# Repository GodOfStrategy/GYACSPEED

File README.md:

# GYACSPEED
Speedometer, accelerometer and a gyroscope for my bicycle, with the XIAO RP2040 as the MCU, with a 2.4" TFT (no touchscreen) display (connected with jumpers) for the information.
I saw the Hermes starter project and though, "Why only stop at a gyroscope?" and then answered my own question by adding a speedometer powered by the Ublox NEO-M9N GNSS module, and a gyroscope and an accelerometer powered by the LSM6DSLTR!! So that I can see my speed, acceleration, and how I take turn using the gyroscope and such, with the XIAO RP2040 serving as my MCU. I made this project because, well, I thought that Hermes was cool but then realized that only a gyroscope isn't that useful after all. I thought about an all-in-one bicycle dashboard, complete with a speedometer, odometer (calculated from the GPS module), accelerometer (to see the derivative of velocity ;) ). My bicycle isn't really a smart bicycle so it doesn't have all these features built-in like some other smart bicycles.
So, I drew the Schematics:

Then I routed the PCB

How my assembled PCB is supposed to look like:

Then I designed a case in Fusion 360 for my project, and found solutions so as to how will I mount it on my bicycle and then came up with this monstrosity:

The idea of the mount is to be modular and help me join the two parts by using a single mount. The mount is based on the idea of mounting the project on my bicycle handle bar. I took some measurements and made a cylinder with walls which would wrap around my bicycle bar. After that I added an extension to the cylinder with a flat base, where I added the screw holes. I then added a triangular kind of part to join the cylinder with my main project case.

Instructions on Assembling:
1. Solder the Header Pins.
2. seat the pcb into the top case.
3. Now there is an opening in the bottom of the top case to allow jumpers from the Li-Po to connect with the Main PCB as shown here: 
4. The hole on the side of the bottom [battery] case looks like so: 
5. Run two jumpers connecting the Battery to the PCB, the left pin on the main PCB is the +ve terminal, as mentioned on the silkscreen.
6. There are mounting holes on tft module that I will be purchasing, and I have also added holes on my case top so that I can secure the display. To do so, we place the Display on the bottom of the top case like so:  and then insert bolts(M3/ 15mm) form the top : and screw them with the nuts tightly.
7. Then we again use jumper wires to connect the display to the pcb 
after which we place the top case cover on the top case and put 30 mm M3 bolts through the screw holes and secure them with M3 nuts.
8. For the bottom case, we insert our battery in the main bottom case, run the jumpers to the main PCB through the openings, and then We put the case cover on, and screw it using M3 30mm bolts and M3 nuts.
9. Now, we have two modules, to mount them together on a bicycle handlebar, we simply put them on the bicycle bar and then screw the both together in this mount-ish-part 
using the screw holes, and M3 15mm bolts along with M3 nuts.
Thats it! You're done

Here is my BoM (which you can find in the root of my repository as well):

|Designator|Footprint|Quantity|Value|LCSC Part #|Price (US $)|Links|Distributor|Generic Name|
|---|---|---|---|---|---|---|---|---|
| C1 | 805 | 5.0 | 100uF |  | 3.54 | GRM21BR60E107ME15K Murata Electronics \| Mouser India | Mouser India | Capacitors |
| C10, C3, C4, C5 | 402 | 10.0 | 10uF |  | 0.46 | https://www.mouser.in/ProductDetail/TAIYO-YUDEN/MSASJ105CB5106MFNC12?qs=PBDs2xEllI8xKzMj03Wyvw%3D%3D | Mouser India |  |
| C11, C12, C7, C8, C9 | 402 | 5.0 | 0.1uF |  | 0.24 | https://www.mouser.in/ProductDetail/80-C0402C104K4P | Mouser India |  |
| C2 | 402 | 1.0 | 1pF |  | 0.25 | 04023A1R0DAT2A KYOCERA AVX \| Mouser India |  |  |
| C6 | 402 | 10.0 | 1uF |  | 0.17 | https://www.mouser.in/ProductDetail/KYOCERA-AVX/0402X5R105KTAAT?qs=XAiT9M5g4x9uZyL2wCxs9w%3D%3D | Mouser India |  |
| D1 | D_SMA | 3.0 | SS14 |  | 1.3 | https://www.mouser.in/ProductDetail/onsemi/SS14?qs=mVVXn4M53U%252BvrBaFv5vr4w%3D%3D | Mouser India | Reverse Polarity Protection diode |
| DS1 | TFT LCD 240x320 2.4" | 2.0 | TFT LCD 2.4" SPI |  | 16.53 | [https://www.amazon.in/Tishvi-Interface-Contrast-Microcontroller-Projects/dp/B0GZQBH8TX/ref=sr_1_5?](https://www.amazon.in/SmartElex-2-4-inch-Interface-Resolution-Embedded/dp/B0GFD2GKS3/ref=sr_1_4?crid=244DTUY4MZBQU&dib=eyJ2IjoiMSJ9.mDHIa2KAK2pmYUCsQJKHijIuZuYtAhf37UUXZ595NunUV92PkwKzGlaTkl74UG3vta_Y1FTv8jmFhQ4SpozWyYBP9G75R6iKsYMW7jx-yHz3v-XOoo8-NUCHxRbKeTt5cD8Obvwvtn8YszEZtxFSuAXtiARzswfbkZinJIO2O0KPUdrK37qG1dR4FZ4mwfbZ0ufkE-BBbzZWaG5fWrOaPU771ftGh-Zgijp7mwLvgODtW0shDh-DNo6jAhYBoJCUGXP24-NSn2eDBEwA2ogDf_CD-Ctqugaj9IkxcIXHBB4.f5dMLYGoDtHfcPthudfcRWmNg96l1DWC8e63EOn9BP8&dib_tag=se&keywords=3+inch+tft+lcd&qid=1785163110&sprefix=3+inch+tft+lc%2Caps%2C434&sr=8-4)crid=5ELFGR2Y3AVB&dib=eyJ2IjoiMSJ9.Jpr0nalYGfL14nV7bbjmTZKJv2EIKupA4PS6ncRHPeflKUuEP1chaxLUuG31tnS91O83QhHNpJtINdHxloWLYH9lf4NJ4qSOWR6nymU5ejpQAXrm3idjtpBYQ0aIwBILTmNX_3lALKvsE76wo-qvywPqliJmu2u1Sw0mh8OCet7xKizlRF5dPz3CHCYLgBtFUnNA9Eu-mYQBGu7QWCQPqbfzEN95b4kUAEvBXaaM7DjF16ZafKrP9sBf0yOEFYHzo9n5p0J-zkTF9JNQ7vyMX4nY2xR5RTSpoe2_mFh8lyM.-pu-_CBvqfhh_vnW6SlNHAERV8AtyvnIy9OJlCs-LRc&dib_tag=se&keywords=1.3%22+OLED+IIC&qid=1782751854&sprefix=1.3+oled+iic%2Caps%2C282&sr=8-5 | Amazon India | OLED |
| E1 | XCVR_ANT-GNCP-TH25AL12 | 2.0 | ANT-GNCP-TH25AL12 |  | 22.2 | https://www.mouser.in/ProductDetail/TE-Connectivity/ANT-GNCP-TH25AL12?qs=A6eO%252BMLsxmRfsTs3t3ApUw%3D%3D | Mouser India | Passive antenna |
| J1, J2 | PinHeader_1x05_P2.54mm_Vertical | 0.0 | Conn_01x05_Pin |  | 0.0 |  | Self-Sourced |  |
| J3 | PinHeader_1x02_P2.54mm_Vertical |  | Conn_01x02_Socket |  |  |  |  |  |
| L1 | 603 | 1.0 | 1 uH |  | 0.52 | https://www.mouser.in/ProductDetail/ABRACON/AIML-0603-1R0K-T?qs=1vO2EIVe%252BY7DV5QHOd2BCw%3D%3D | Mouser India | Inductor |
| Q1, Q2 | SOT-23-3_L3.0-W1.7-P0.95-LS2.9-BR | 4.0 | SI2301CDS-T1-GE3 | C10487 | 3.47 | SI2301CDS-T1-BE3 Vishay / Siliconix \| Mouser India | Mouser India | MOSFETs |
| R1 | 402 | 1.0 | 453K |  | 0.088 | RC0402FR-07453KL YAGEO \| Mouser India | Mouser India | Resistors |
| R2 | 402 | 1.0 | 100K |  | 0.37 | https://www.mouser.in/ProductDetail/YAGEO/AC0805JR-7W100KL?qs=r5DSvlrkXmI4dHdBm%2FLHKQ%3D%3D | Mouser India |  |
| R3 | 402 | 1.0 | 2.2K |  | 0.078 | RC0402JR-7D2K2L YAGEO \| Mouser India | Mouser India |  |
| R4 | 402 | 1.0 | 330 |  | 0.078 | CR0402-JW-331GLF Bourns \| Mouser India | Mouser India |  |
| U1 | XIAO-RP2040-DIP | 2.0 | XIAO-RP2040-DIP |  | 10.57 | https://www.mouser.in/ProductDetail/Seeed-Studio/102010428?qs=Znm5pLBrcAJ75FCbdxzDHQ%3D%3D | Mouser India | MCU |
| U2 | XCVR_NEO-M9N-00B | 2.0 | NEO-M9N-00B |  | 23.69 | https://www.mouser.in/ProductDetail/u-blox/NEO-M9N-00B?qs=DPoM0jnrROVeJ6BHpcwcjw%3D%3D | Mouser India | GNSS Module |
| U3 | LGA-14_3x2.5mm_P0.5mm_LayoutBorder3x4y | 2.0 | LSM6DS3 |  | 13.42 | https://www.mouser.in/ProductDetail/STMicroelectronics/LSM6DSV32XTR?qs=HoCaDK9Nz5d%252BGVBpjxkjlg%3D%3D | Mouser India | 3D Gyroscope + Accelerometer |
| U4 | VQFN-7_L2.0-W2.0-P0.55-TL_RWU | 2.0 | TPS61022RWUR | C915088 | 6.31 | TPS61022RWUR Texas Instruments \| Mouser India | Mouser India | Swirching Buck Regulator |
| U5 | WSON-6_L1.5-W1.5-P0.50-TL | 2.0 | BQ29703DSER | C2876295 | 1.12 | BQ29703DSER Texas Instruments \| Mouser India | Mouser India | Battery overdischarge protection |
|  |  | 1.0 | (cheaper and better than any hotplate on amazon[reviews for the hotplate were horrible]) |  | 37.02 | https://www.amazon.in/Soldering-600W-Adjustable-Temperature-Electronics/dp/B0DT693N47/ref=sr_1_6?crid=I17ZBO9TIH25&dib=eyJ2IjoiMSJ9.FsdtfVoczd9shIGi1JidgTFhVZU3PFvoQGJldGg7Cpv5ksv4-U_6kbnfS4mtH0jhhWiM1jRQhNFOnu4Q0drOVU3rrWNbptRJktia4E1s4IR5OQi9mv0mg5h_zZlmy8v4W2ylUXS-yZ-ujxIA_keNFwOfES78w1ame4wQulRuZtnQF2HklhbvLX5QGb208EzBce009oSOCJIe30eZxFItGCZDVPvRNO2Iiu3Kn373kkNJ_hPoHMywojWR262_uksQwLGUpWi2Yoih77FJG2c-cx431YMeGKAyr-9FrJgppy4.1wxK7OY-Kkgp5AmE_xG48WUq_anGH8X6GXZ9NE3hOS4&dib_tag=se&keywords=hot%2Bair%2Bsoldering%2Bstation&qid=1782751732&sprefix=hot%2Bair%2Bsoldering%2Bstatio%2Caps%2C260&sr=8-6&th=1 | Amazon India | Hot air gun [ 2 in 1] |
|  |  | 1.0 |  |  | 6.34 | https://www.amazon.in/SR-Syringe-Circuit-Assembly-Mechanic-Soldering/dp/B0H511T6TD/ref=sr_1_48?crid=3P3DC8P9NHW0L&dib=eyJ2IjoiMSJ9.aEk180-YLG3lQI1k73US-jzt3Ih5h-liHr-43e85lFqNNFX1Ds1VlW6CLfQzOfbndOtC68nkvJScAlmXhe5nvIoegC8YD5CLVkUvp1UlEwYwxRwS0b3Z1AWv3d13BfoRDN6LNLwd_S8YC8jqkzKCpTbeFd3loFNtHf1zGmwtNd7mplBqoIE9Od8t0OT74216Nm7bwbbY7Ky3tAleIcoPGMEhKf_EpLjs6108kMM29epkaSWYoZ0EXBH_6NjJPxSqrv1NGVC89srmXZGQ4aSEfiRcHuqAV4l2AXCjiMLTHII.1-TN1lKNicga31AGBN0b6FXjaPlUQCZZS_PRh4iUGlY&dib_tag=se&keywords=soldering+paste&qid=1782751406&sprefix=soldering+past%2Caps%2C270&sr=8-48 | Amazon India | Soldering Paste |
|  |  | 1.0 |  |  | 4.75 | https://www.amazon.in/Desoldering-Microprocessor-Smartphones-Motherboards-Electronic/dp/B0C7N66JFQ/ref=sr_1_1_sspa?crid=1VAETTJLUCO3M&dib=eyJ2IjoiMSJ9.hOiPJ7rgOjPztQWsPo8jhoggBpaMklr7kvcrpSIjwOVkLl16IKyNLYuDcDdrpQWDrYo71Vki124_7-mIntjB5E0qychsMRDrkd9QibGbS6k2q1XBAmRiK50UZibHWWLdXUw32geY6KOZEQ3Z-GXVFxnyr-3uQ33OBiMgQvh8uCLNI5_HKipHOXwNvYoy3lVM-yILMCYRSjPZGBA-OepBmQY7YRSGq8K25ZiAcehMwcNKed5oWdBEeWaNEiPAC_mxB6PYmUQxSHRdg8r6PEQ22DbTabW6DNp8nSZiWxR11TU.BXbx8OQ2AQXUbj0qAa8IyBWaVqeFlPbLyliTOwFZbUQ&dib_tag=se&keywords=flux+liquid&qid=1782751559&sprefix=flux+liqui%2Caps%2C281&sr=8-1-spons&aref=HU8aJacmGB&sp_csd=d2lkZ2V0TmFtZT1zcF9hdGY&psc=1 | Amazon India | Flux Paste |
|  |  | 10.0 |  |  | 2.91 | https://www.amazon.in/Rpi-shop-Phillips-Countersunk-Quantity/dp/B08HNBTZ3D/ref=sr_1_2?crid=182PW1ULT5V52&dib=eyJ2IjoiMSJ9.SO-oK_EvJrxhcPvSBwAID9oN8aPfZMD2sN3wlqsuNDrsUX_B3TlkGuszDxjUG1ZexYkQ0ta6jm6bYPIXN8d1xIKtCjd-jDtH7MdE1n8-QVYJO-xCzczKZx7GVnAbwClLtWI4IA1saaYmm6J_ii7HyHAbH9nU-24gh5vEJ-q148JzgNf-15xCOnVgcM1GLAtrTDy8uD375GTlWTFaR4ysRj-t18uC3Tn264Kwo-eOfOuoNJtt2daXsOiYcvHtvh6OFHMRqhSkW6Rfkb23LvRZbSUR1E3rOUDxi5yDxPFmHhk.khCUfvzpo39N2k34vDU6Q4tqYPMJAbTftGCj0PBAi3g&dib_tag=se&keywords=M3+15mm&qid=1782751337&sprefix=m3+1mm%2Caps%2C272&sr=8-2 | Amazon India | M3 bolts 15mm |
|  |  | 30.0 |  |  | 3.7 | https://www.amazon.in/Invento-pcs-Head-Screws-Projects/dp/B073Z9LXB2/ref=sr_1_6?crid=17K8U5W20KVAU&dib=eyJ2IjoiMSJ9.8Rr-G5CMR7WPuXRa3Uqc0ZywjGzR_ZVxk9Zv9TwC2NaFyXYnLSveKUurI6PVoUxeYTrcG9jWLz0rgCj5AFCso8gaRj5qwJfLi9x3OOJ2zw3P1nP-F895WtWeOa1HRsKD2Hn_LCypdER8pZH1oLG066aQ6pjOVofzx51ZsNDLH41by6vkpNWzvlViWt1l7dSCZbBEXhDIjyYBwyOBU4B_XWMwUsaHgVnCDJJV7nUe1bC5PUQnFsFZmiyCzbICNLFlbmyX8h18THg0NFtYWBoUJnHMAHgKGrfSAgqJDxpHPus.GXIMaNEWZWcUNZcVlyDOw5mL5-QaePaRx0PsgHQ7w5E&dib_tag=se&keywords=M3+30mm&qid=1782751265&sprefix=m3+30m%2Caps%2C265&sr=8-6 | Amazon India | M3 bolts 30mm |
|  |  | 50.0 |  |  | 1.51 | https://www.amazon.in/TRO-M3-3mm-HEX-NUT-SS304-PACK/dp/B0DSWCH2XN/ref=sr_1_5?crid=FVR2RZ51YX4H&dib=eyJ2IjoiMSJ9.feK43w_iaXaS0XNaKPL5kHwMh0uDDsJCjnM_0tjJLCI0Up2GdM2CmW6sKvQl3regV4jQqe1qf7fsynv4ocPOGZCLt9lgX3EttZ9PLu9LjYI__AXgqcvcxDSKr7AIYHlJXlEZn7S4YFi9-utV9D1o2PkpLEd8Mpn5KBq35H_6-DIb48Oa2TN5Kxamjto5qw1ZtFD3OfGBNK0g-DyQA1e2rXPJH1gukXVtqfjVqcxg6G7t4FKUsBcI1kIhUqNadzupf1LEt2i-R53mHB5ytZzuob55t_i9NVmlKxMrkwj1PoQ.tHX4G2rxo5U4V4dk2mUMQg5EyAiwbmTxpBVn9Ly0W2g&dib_tag=se&keywords=M3%2Bnuts&qid=1782751369&sprefix=m3%2Bnut%2Caps%2C258&sr=8-5&th=1 | Amazon India | M3 nuts |
|  |  | 10.0 |  |  | 0.93 | https://www.amazon.in/Female-2-5mm-Cable-Connector-Silicone/dp/B0837W4DC8/ref=sr_1_5?crid=3LHOA6EZRAI01&dib=eyJ2IjoiMSJ9.HRrdV8G2Uo9Pr-3CvDLoiJcQAXXaR8DsYSDTa_uNgd0GXNEr6xPyKmYxJ0OiOMOU8GzLozjxiHKJhJOxks7Sioq8_NLP8qPdKUCAt5RqVpd-Lg9K3U1amXUhnzFaONAcuPjxKKZJCY6rhkUtL6iTEHzjOi9Q2fxZ_gkYFmIeSp1Z8_MVvBOM3ZJAK6b38diDG4cBJGB8RR6LT2r-vaaKFHjR9jVgk-8hiA6ir0TafvRS97PLvF-zxbK7_ejoPSDjeeyRgniOC6QixrTtt4E9pdbSD-u16pwOKXliysNH60o.7WR11O6wnsQGLpdZ3TC4k8Oe34nOCeA_kMKdlOsuqCk&dib_tag=se&keywords=jst+connector&nsdOptOutParam=true&qid=1782751626&sprefix=jst+connect%2Caps%2C263&sr=8-5 | Amazon India | 2 pin 2.5mm Cable Micro Male and Female Connector Plug For Lithium Ion Battery connector |
|  |  | 1.0 |  |  | 6.31 | https://www.amazon.in/ELBOTICS-Rechargeable-Lithium-ion-Electronics-Helicopter/dp/B0F4KQPNNH/ref=sr_1_2_sspa?dib=eyJ2IjoiMSJ9.uuI3ErDTGOj_mpnSD0xCatKsXyF6WcqN3ys1CSv8hymvyHlkeWc8Sz7AMxMOHCPd0BYYTrCZUVPUhTH9WCTtNaxHl0py9d6xxfU1ZM4iaw6evrQt6M4kX6IwnjXLAqKkzoXkcUMlx9bUHy2tZzjfHnig2VuzWGmgh-ivHoZ6i-oMqpQr-0QnIj0lJt9pzDTRdrs0e-2eg9bdqIcpnB-2JN-oIlOgX1YtGLQYt2vhjRg.WUZHsHvkRsij_90KECGZMW7y-ViZizv_9SP6Oeo5MWA&dib_tag=se&keywords=7.4V%2BLiPo%2B2000maH&qid=1779173194&sr=8-2-spons&aref=7izaQucMVA&sp_csd=d2lkZ2V0TmFtZT1zcF9hdGY&th=1 | Amazon India | 2 cell LiPo [2000 maH] |
|  |  | 1.0 |  |  | 1.66 | https://www.amazon.in/Step-Up-Overvoltage-Protection-Efficiency-Electronics/dp/B0FDRCPRM8/ref=sr_1_8?crid=1AUEEGM3JGUWH&dib=eyJ2IjoiMSJ9.w4H_TYeTydAPA4H-ny1v9JMhcIYUUiamgJEf57YUnLDjHTLmyq4bDnVYqFx_EoJV17b992dQvipaoyoCsWOfIkRPdW_0kJEaTHwnzfvly6XT5U85fp2clvX2y6GjWRKZQQry5x7-hcMSNh8Vd-IH8oJO74vum1ciWdXd-80mVHXNMjJfcs5Tw-P8knBYZnXG6AGThSdx-kR7erMgZi6dJLWPzbcbdNY35rHgV4u0p6gLLT64m13QhR-ggX2Pg_lfRSW9bPVNyBJgPm4cQqwwCcLc0i3n9ulcBGUvfm_cukw.cWKO_71gcsYAqjd1FaOotepXvfM4YS7cM5IoLp1Mot8&dib_tag=se&keywords=2+cell+lipo+charger&qid=1782751684&sprefix=2+cell+lipo+charge%2Caps%2C259&sr=8-8 | Amazon India | 2 cell LiPo Charger |
|  |  | 1.0 |  |  | 21.58 |Shipping|  | SHIPPING (Mouser +JLCPCB) |
|  |  | 5.0 |  |  | 5.0 |PCBs from JLCPCB|  | PCB |
|  |  | 1.0 |  |  | 7.16 |Stencil so that I can solder them myself|  | Stencil |
|  |  |  |  |  |  |  |  |  |
|  | TOTAL --> |  | 203.89 $|  |  |  |  |  |

[bom(final).csv](https://github.com/user-attachments/files/29474485/bom.final.csv)

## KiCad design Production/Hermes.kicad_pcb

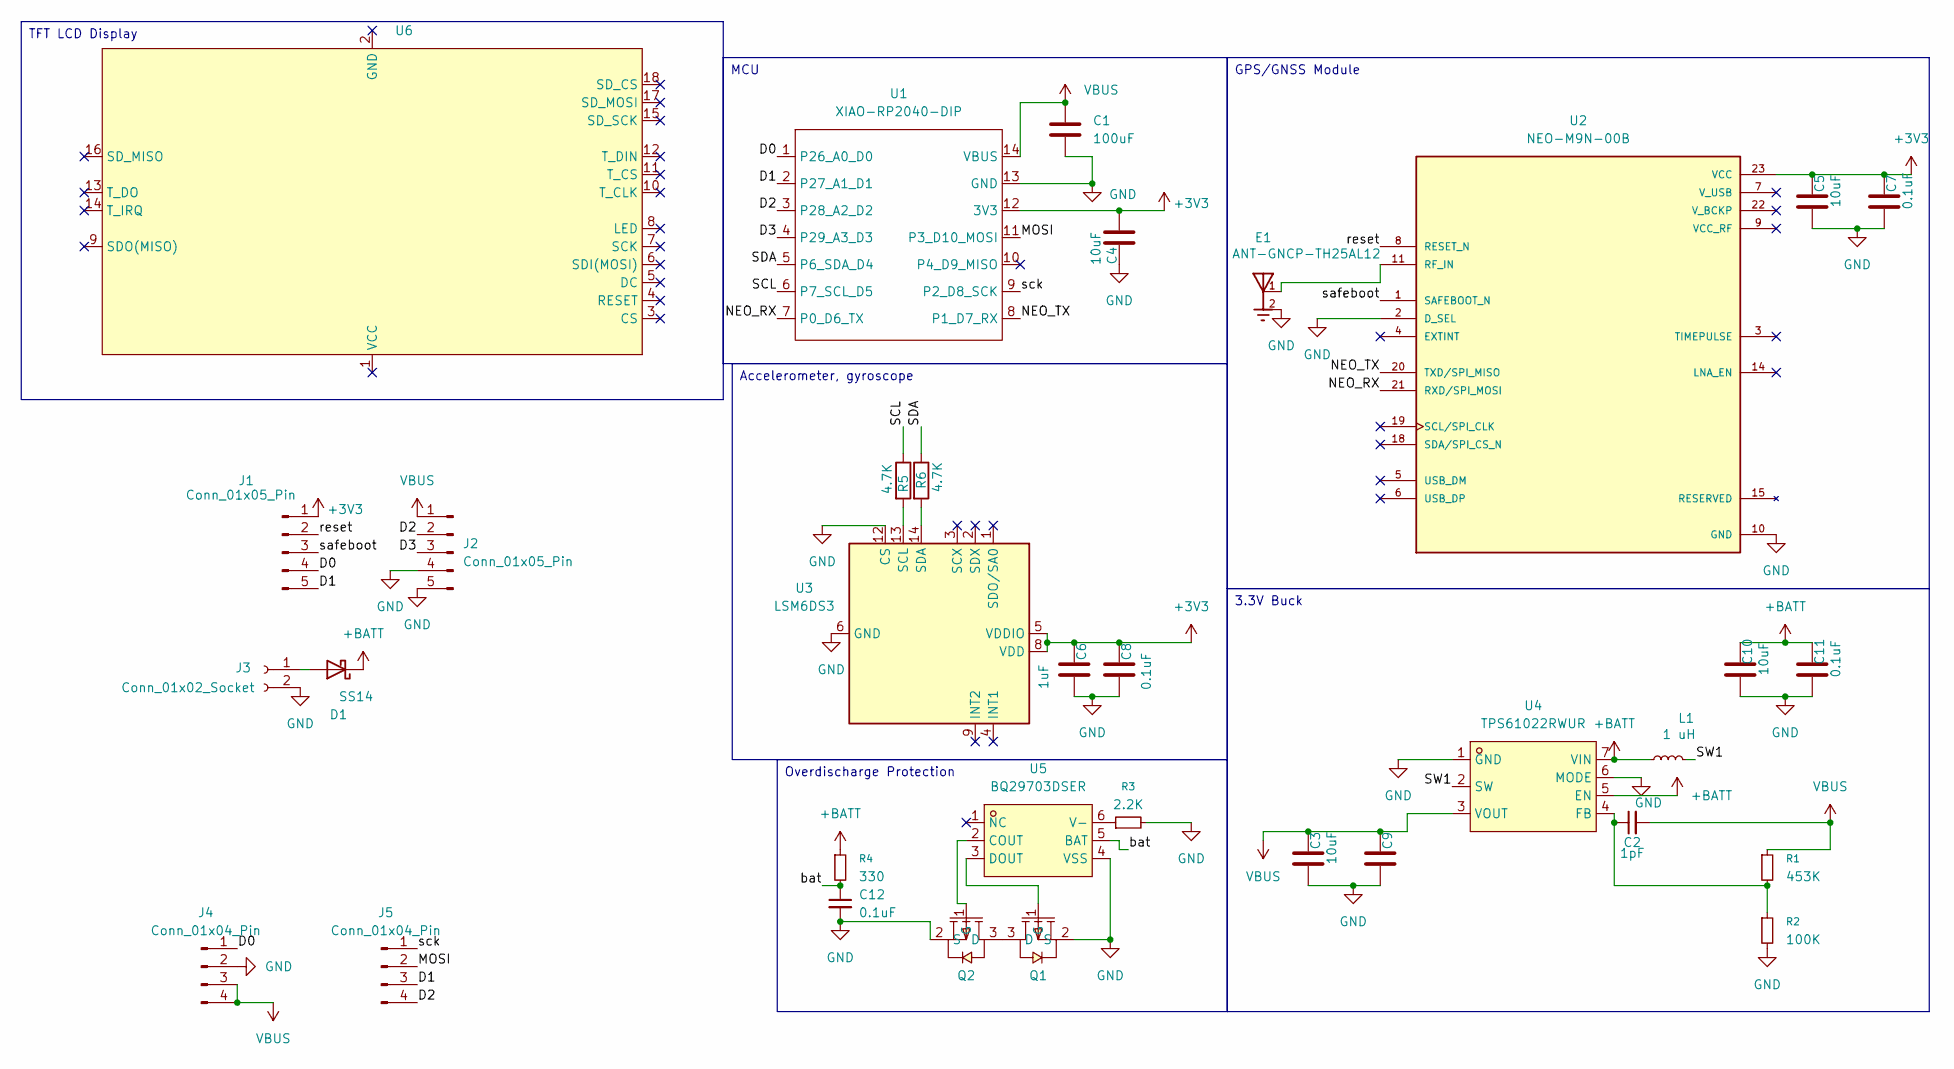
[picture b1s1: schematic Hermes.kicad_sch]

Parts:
C1: 100uF; C_0805_2012Metric
C2: 1pF; C_0402_1005Metric
C3, C4, C5, C10: 10uF; C_0402_1005Metric
C6: 1uF; C_0402_1005Metric
C7, C8, C9, C11, C12: 0.1uF; C_0402_1005Metric
D1: SS14; D_SMA
E1: ANT-GNCP-TH25AL12; XCVR_ANT-GNCP-TH25AL12; PARTREV A
J1, J2: Conn_01x05_Pin; PinHeader_1x05_P2.54mm_Vertical
J3: Conn_01x02_Socket; PinHeader_1x02_P2.54mm_Vertical
J4, J5: Conn_01x04_Pin; PinHeader_1x04_P2.54mm_Vertical
L1: 1 uH; L_0603_1608Metric
Q1, Q2: SI2301CDS-T1-GE3; SOT-23-3_L3.0-W1.7-P0.95-LS2.9-BR; MPN SI2301CDS-T1-GE3; LCSC Part C10487
R1: 453K; R_0402_1005Metric
R2: 100K; R_0402_1005Metric
R3: 2.2K; R_0402_1005Metric
R4: 330; R_0402_1005Metric
R5, R6: 4.7K; R_0402_1005Metric
U1: XIAO-RP2040-DIP
U2: NEO-M9N-00B; XCVR_NEO-M9N-00B; PARTREV R05
U3: LSM6DS3; LGA-14_3x2.5mm_P0.5mm_LayoutBorder3x4y
U4: TPS61022RWUR; VQFN-7_L2.0-W2.0-P0.55-TL_RWU; MPN TPS61022RWUR; LCSC Part C915088
U5: BQ29703DSER; WSON-6_L1.5-W1.5-P0.50-TL; MPN BQ29703DSER; LCSC Part C2876295
U6: 2.4'' 240x320 LCD Display TFT Module; 2.4_240x320_LCD_Display_TFT_Module

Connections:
+3V3: C4.2, C5.1, C6.1, C7.1, C8.1, J1.1, U1.12 (3V3), U2.23 (VCC), U3.5 (VDDIO), U3.8 (VDD)
+BATT: C10.1, C11.1, D1.1 (K), L1.1, R4.1, U4.5 (EN), U4.7 (VIN)
/D0: J1.4, J4.1, U1.1 (P26_A0_D0)
/D1: J1.5, J5.3, U1.2 (P27_A1_D1)
/D2: J2.2, J5.4, U1.3 (P28_A2_D2)
/D3: J2.3, U1.4 (P29_A3_D3)
/MOSI: J5.2, U1.11 (P3_D10_MOSI)
/NEO_RX: U1.7 (P0_D6_TX), U2.21 (RXD/SPI_MOSI)
/NEO_TX: U1.8 (P1_D7_RX), U2.20 (TXD/SPI_MISO)
/SCL: R5.1, U1.6 (P7_SCL_D5)
/SDA: R6.1, U1.5 (P6_SDA_D4)
/SW1: L1.2, U4.2 (SW)
/bat: C12.1, R4.2, U5.5 (BAT)
/reset: J1.2, U2.8 (RESET_N)
/safeboot: J1.3, U2.1 (SAFEBOOT_N)
/sck: J5.1, U1.9 (P2_D8_SCK)
GND: C1.2, C3.2, C4.1, C5.2, C6.2, C7.2, C8.2, C9.2, C10.2, C11.2, C12.2, E1.2, E1.3, E1.4, E1.5, J2.4, J2.5, J3.2, J4.2, Q1.2 (S), Q2.2 (S), R2.2, R3.2, U1.13 (GND), U2.2 (D_SEL), U2.10 (GND), U2.12 (GND), U2.13 (GND), U2.24 (GND), U3.6 (GND), U3.7 (GND), U3.12 (CS), U4.1 (GND), U4.6 (MODE), U5.4 (VSS)
unnamed: D1.2 (A), J3.1
unnamed: Q1.3 (D), Q2.3 (D)
unnamed: Q1.1 (G), U5.3 (DOUT)
unnamed: Q2.1 (G), U5.2 (COUT)
unnamed: E1.1, U2.11 (RF_IN)
unnamed: R5.2, U3.13 (SCL)
unnamed: R6.2, U3.14 (SDA)
unnamed: C2.1, R1.2, R2.1, U4.4 (FB)
unnamed: R3.1, U5.6 (V-)
VBUS: C1.1, C2.2, C3.1, C9.1, J2.1, J4.3, J4.4, R1.1, U1.14 (VBUS), U4.3 (VOUT)

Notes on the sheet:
GPS/GNSS Module
MCU
Accelerometer, gyroscope
TFT LCD Display
Overdischarge Protection
3.3V Buck

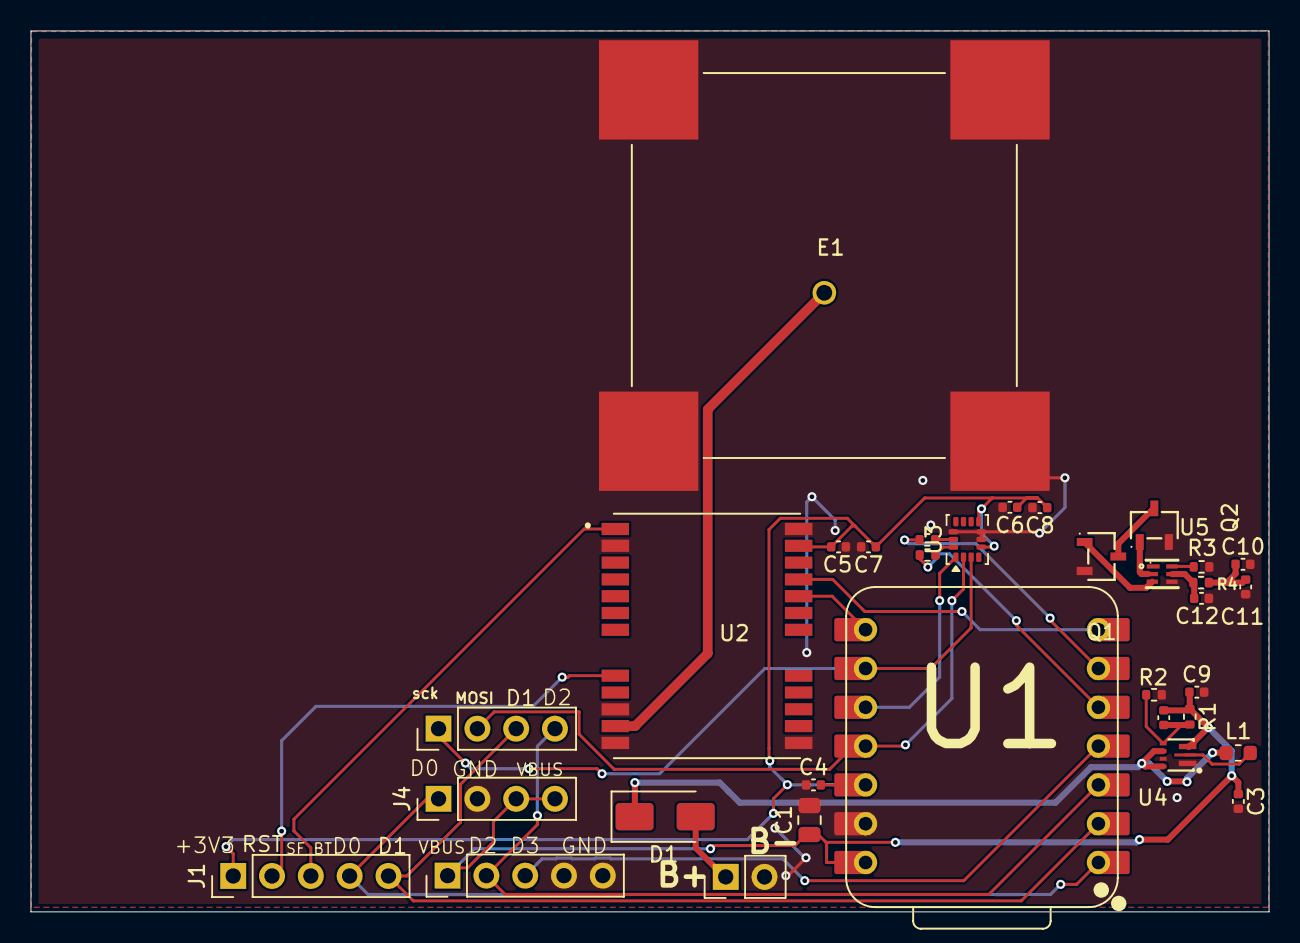
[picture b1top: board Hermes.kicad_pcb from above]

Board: 2 copper layers, 81.0 x 57.7 mm, 33 parts (0 on the bottom side), 27 nets.

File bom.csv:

Designator,Footprint,Quantity,Value,LCSC Part #,Price (US $),Links,Distributor,Generic Name
C1,805,5,100uF,,3.54,GRM21BR60E107ME15K Murata Electronics | Mouser India,Mouser India,Capacitors
"C10, C3, C4, C5",402,10,10uF,,0.46,https://www.mouser.in/ProductDetail/TAIYO-YUDEN/MSASJ105CB51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,Mouser India,
"C11, C12, C7, C8, C9",402,5,0.1uF,,0.24,https://www.mouser.in/ProductDetail/80-C0402C104K4P,Mouser India,
C2,402,1,1pF,,0.25,04023A1R0DAT2A KYOCERA AVX | Mouser India,,
C6,402,10,1uF,,0.17,https://www.mouser.in/ProductDetail/KYOCERA-AVX/0402X5R105KT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,Mouser India,
D1,D_SMA,3,SS14,,1.3,https://www.mouser.in/ProductDetail/onsemi/SS14?qs=mVVXn4M53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,Mouser India,Reverse Polarity Protection diode
DS1,LCD_OLED_128X64_1.3_I2C,2,OLED_128X64_1.3_I2C,,5.66,https://www.amazon.in/Tishvi-Interface-Contrast-Microcontrol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,Amazon  India,OLED
E1,XCVR_ANT-GNCP-TH25AL12,2,ANT-GNCP-TH25AL12,,22.2,https://www.mouser.in/ProductDetail/TE-Connectivity/ANT-GNCP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,Mouser India,Passive antenna
"J1, J2",PinHeader_1x05_P2.54mm_Vertical,0,Conn_01x05_Pin,,0,,Self-Sourced,
J3,PinHeader_1x02_P2.54mm_Vertical,,Conn_01x02_Socket,,,,,
L1,603,1,1 uH,,0.52,https://www.mouser.in/ProductDetail/ABRACON/AIML-0603-1R0K-T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,Mouser India,Inductor
"Q1, Q2",SOT-23-3_L3.0-W1.7-P0.95-LS2.9-BR,4,SI2301CDS-T1-GE3,C10487,3.47,SI2301CDS-T1-BE3 Vishay / Siliconix | Mouser India,Mouser India,MOSFETs
R1,402,1,453K,,0.088,RC0402FR-07453KL YAGEO | Mouser India,Mouser India,Resistors
R2,402,1,100K,,0.37,https://www.mouser.in/ProductDetail/YAGEO/AC0805JR-7W100KL?q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,Mouser India,
R3,402,1,2.2K,,0.078,RC0402JR-7D2K2L YAGEO | Mouser India,Mouser India,
R4,402,1,330,,0.078,CR0402-JW-331GLF Bourns | Mouser India,Mouser India,
U1,XIAO-RP2040-DIP,2,XIAO-RP2040-DIP,,10.57,https://www.mouser.in/ProductDetail/Seeed-Studio/102010428?q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,Mouser India,MCU
U2,XCVR_NEO-M9N-00B,2,NEO-M9N-00B,,23.69,https://www.mouser.in/ProductDetail/u-blox/NEO-M9N-00B?qs=DP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,Mouser India,GNSS Module
U3,LGA-14_3x2.5mm_P0.5mm_LayoutBorder3x4y,2,LSM6DS3,,13.42,https://www.mouser.in/ProductDetail/STMicroelectronics/LSM6D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,Mouser India,3D Gyroscope + Accelerometer 
U4,VQFN-7_L2.0-W2.0-P0.55-TL_RWU,2,TPS61022RWUR,C915088,6.31,TPS61022RWUR Texas Instruments | Mouser India,Mouser India,Swirching Buck Regulator
U5,WSON-6_L1.5-W1.5-P0.50-TL,2,BQ29703DSER,C2876295,1.12,BQ29703DSER Texas Instruments | Mouser India,Mouser India,Battery overdischarge protection
,,1,(cheaper and better than any hotplate on amazon[reviews for the hotplate were horrible]),,37.02,https://www.amazon.in/Soldering-600W-Adjustable-Temperature-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,Amazon India,Hot air gun [ 2 in 1]
,,1,,,6.34,https://www.amazon.in/SR-Syringe-Circuit-Assembly-Mechanic-S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,Amazon India,Soldering Paste
,,1,,,4.75,https://www.amazon.in/Desoldering-Microprocessor-Smartphones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,Amazon India,Flux Paste
,,10,,,2.91,https://www.amazon.in/Rpi-shop-Phillips-Countersunk-Quantity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,Amazon India,M3 bolts 15mm
,,30,,,3.7,https://www.amazon.in/Invento-pcs-Head-Screws-Projects/dp/B0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,Amazon India,M3 bolts 30mm
,,50,,,1.51,https://www.amazon.in/TRO-M3-3mm-HEX-NUT-SS304-PACK/dp/B0DSW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,Amazon India,M3 nuts
,,10,,,0.93,https://www.amazon.in/Female-2-5mm-Cable-Connector-Silicone/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,Amazon India,2 pin 2.5mm Cable Micro Male and Female Connector Plug For Lithium Ion Battery connector
,,1,,,6.31,https://www.amazon.in/ELBOTICS-Rechargeable-Lithium-ion-Elec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,Amazon India,2 cell LiPo [2000 maH]
,,1,,,1.66,https://www.amazon.in/Step-Up-Overvoltage-Protection-Efficie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,Amazon India,2 cell LiPo Charger
,,1,,,21.58,,,SHIPPING (Mouser +JLCPCB)
,,5,,,5,,,PCB
,,1,,,7.16,,,Stencil
,,,,,,,,
,TOTAL -->,,192.404,,,,,

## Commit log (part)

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2026-06-27 Create a
